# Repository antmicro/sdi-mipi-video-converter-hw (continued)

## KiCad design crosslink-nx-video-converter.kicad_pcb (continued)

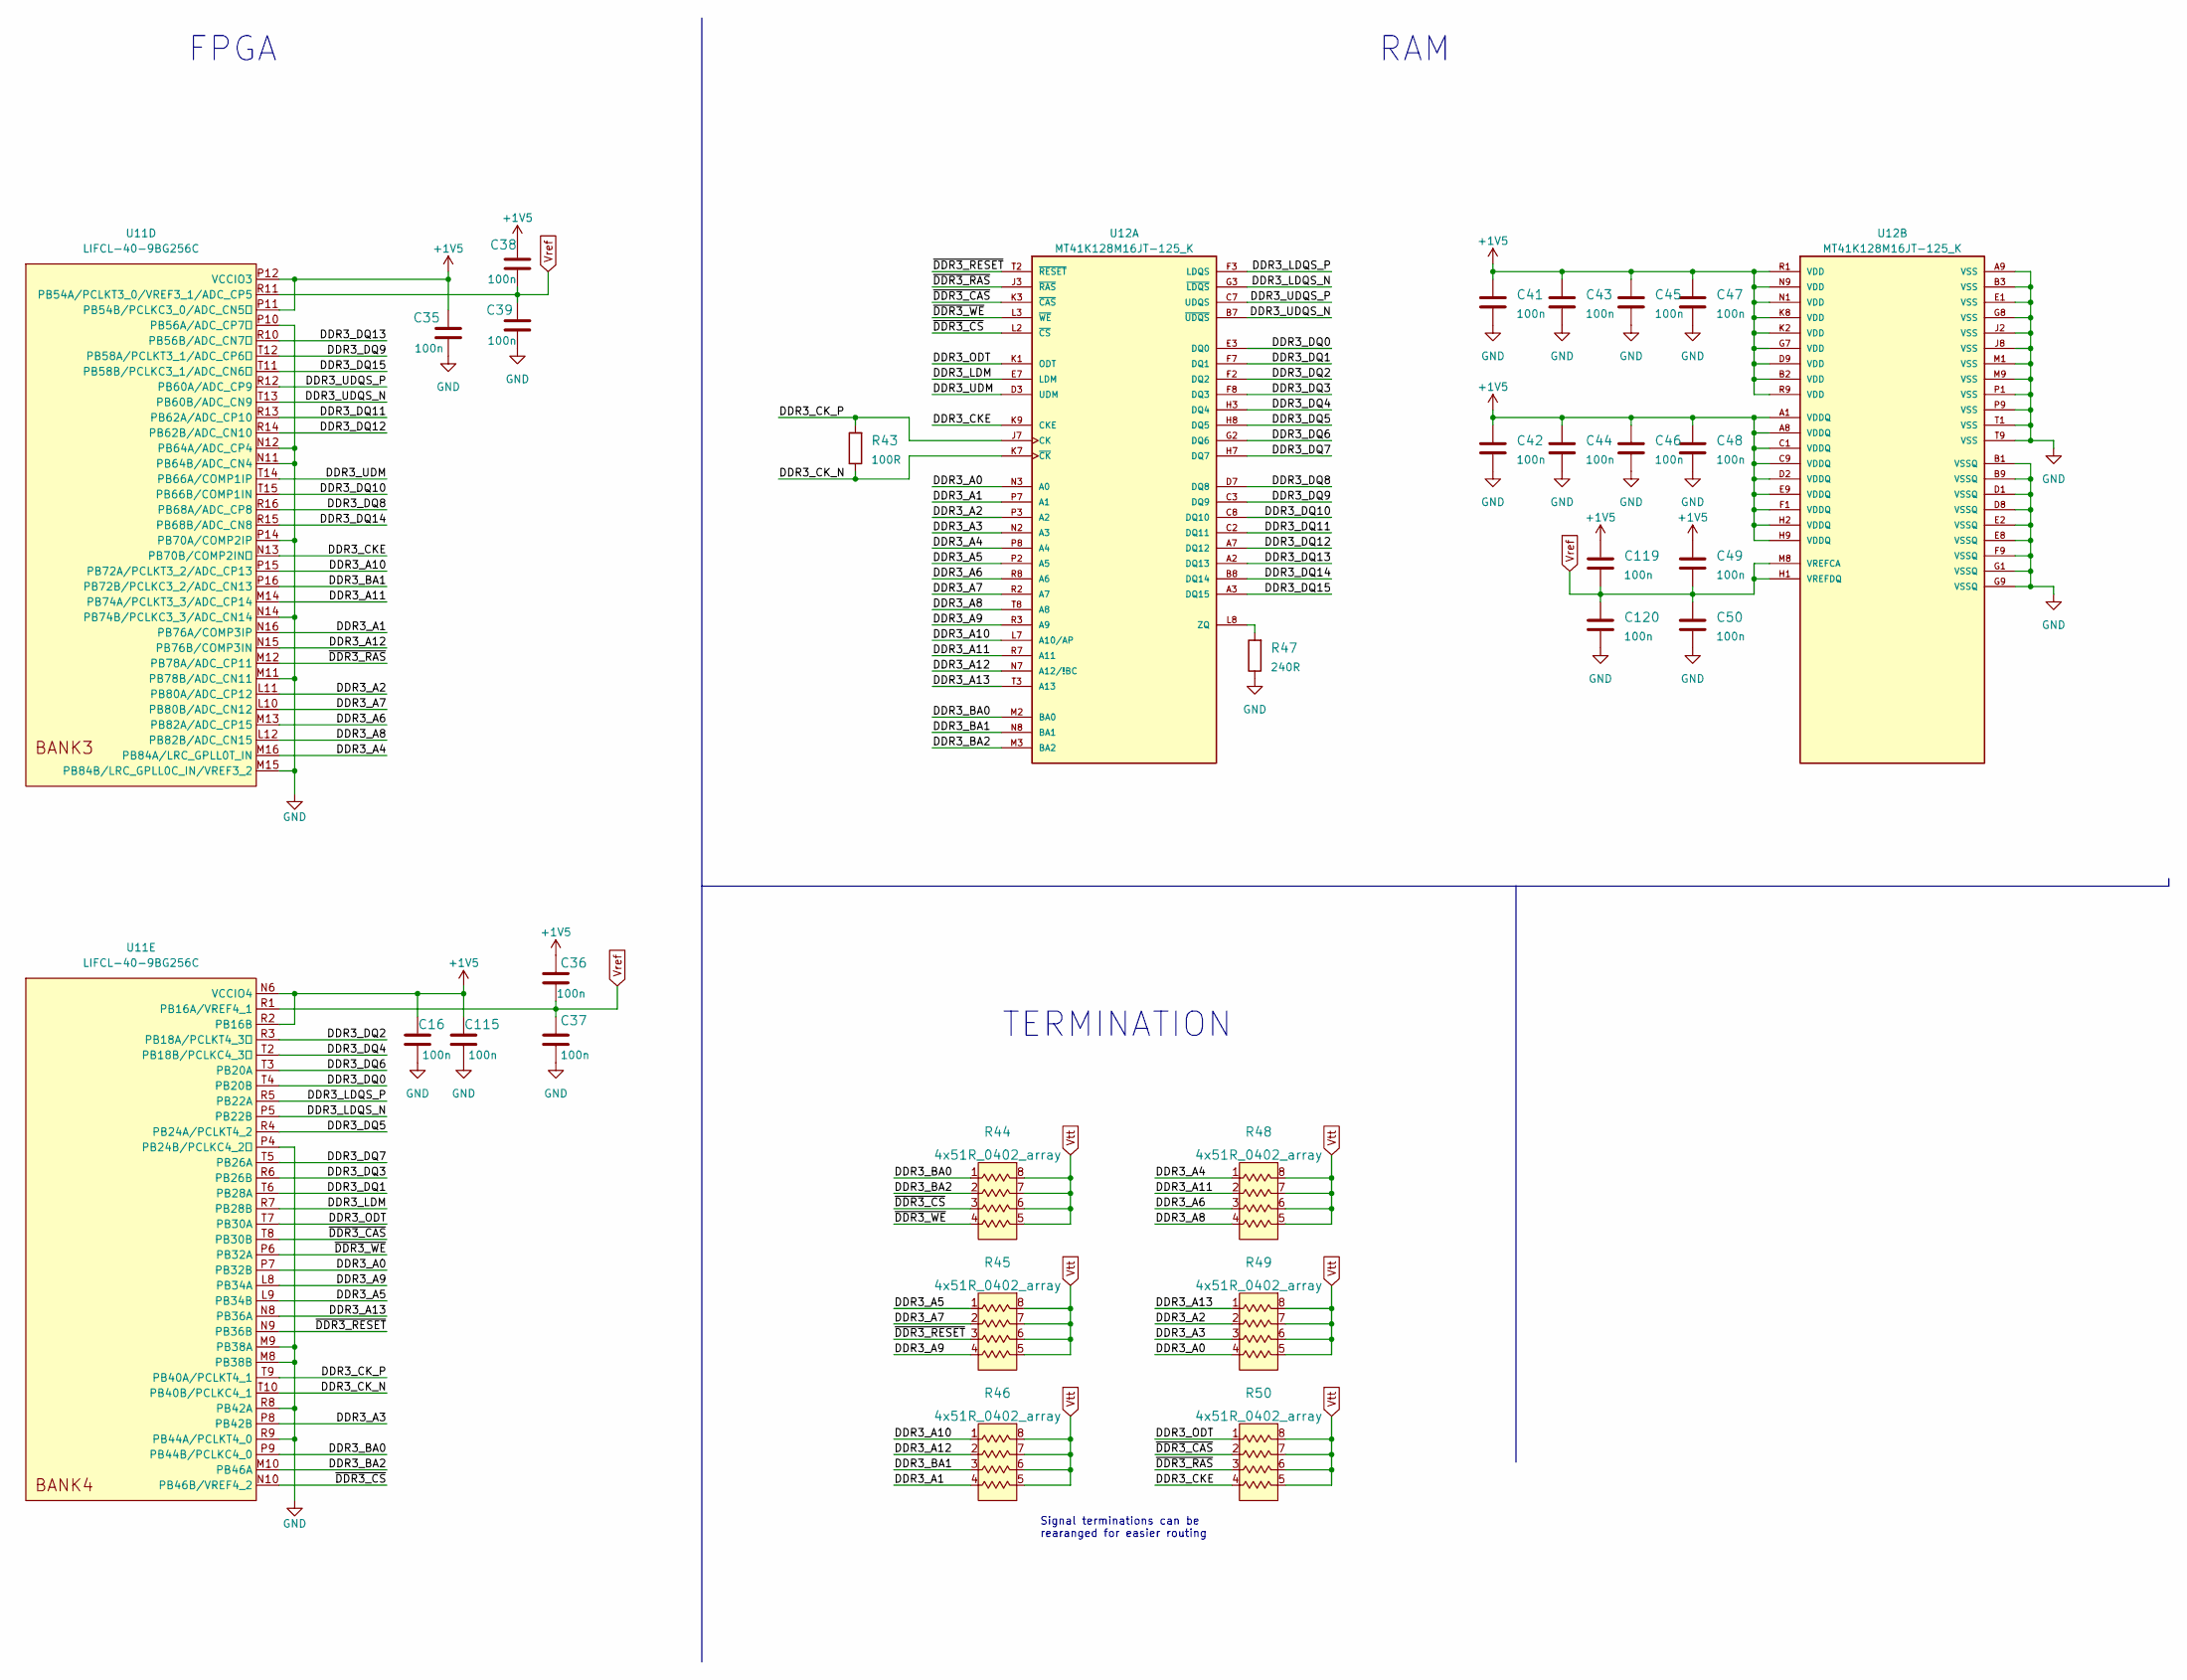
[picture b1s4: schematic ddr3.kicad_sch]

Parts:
C16, C35, C36, C37, C38, C39, C41, C42, C43, C44, C45, C46, C47, C48, C49, C50, C115, C119, C120: C_100n_0402; 0402-cap; MPN GRM155R61H104KE14D
R43: R_100R_0201; 0201-res; MPN CR0201AFW-1000GAS
R44, R45, R46, R48, R49, R50: 4x51R_0402_array; R_Array_4x0402; MPN EXB28V510JX
R47: R_240R_1%_0402; 0402-res; MPN RC0402FR-13240RL
U11: LIFCL-40-9BG256C; BGA-256_16x16_14.0x14.0mm; MPN LIFCL-40-9BG256C
U12: MT41K128M16JT-125_K; BGA80P96C6X16_800X1400X110; MPN MT41K128M16JT-125:K

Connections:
+1V5: C16.1, C35.1, C36.1, C38.1, C41.1, C42.1, C43.1, C44.1, C45.1, C46.1, C47.1, C48.1, C49.1, C115.1, C119.1, U11.N6 (VCCIO4), U11.P11 (PB54B/PCLKC3_0/ADC_CN5), U11.P12 (VCCIO3), U11.R2 (PB16B), U12.A1 (VDDQ), U12.A8 (VDDQ), U12.B2 (VDD), U12.C1 (VDDQ), U12.C9 (VDDQ), U12.D2 (VDDQ), U12.D9 (VDD), U12.E9 (VDDQ), U12.F1 (VDDQ), U12.G7 (VDD), U12.H2 (VDDQ), U12.H9 (VDDQ), U12.K2 (VDD), U12.K8 (VDD), U12.N1 (VDD), U12.N9 (VDD), U12.R1 (VDD), U12.R9 (VDD); also elsewhere on the board
/DDR3/DDR3_A0: R49.4, U11.P7 (PB32B), U12.N3 (A0)
/DDR3/DDR3_A1: R46.4, U11.N16 (PB76A/COMP3IP), U12.P7 (A1)
/DDR3/DDR3_A2: R49.2, U11.L11 (PB80A/ADC_CP12), U12.P3 (A2)
/DDR3/DDR3_A3: R49.3, U11.P8 (PB42B), U12.N2 (A3)
/DDR3/DDR3_A4: R48.1, U11.M16 (PB84A/LRC_GPLL0T_IN), U12.P8 (A4)
/DDR3/DDR3_A5: R45.1, U11.L9 (PB34B), U12.P2 (A5)
/DDR3/DDR3_A6: R48.3, U11.M13 (PB82A/ADC_CP15), U12.R8 (A6)
/DDR3/DDR3_A7: R45.2, U11.L10 (PB80B/ADC_CN12), U12.R2 (A7)
/DDR3/DDR3_A8: R48.4, U11.L12 (PB82B/ADC_CN15), U12.T8 (A8)
/DDR3/DDR3_A9: R45.4, U11.L8 (PB34A), U12.R3 (A9)
/DDR3/DDR3_A10: R46.1, U11.P15 (PB72A/PCLKT3_2/ADC_CP13), U12.L7 (A10/AP)
/DDR3/DDR3_A11: R48.2, U11.M14 (PB74A/PCLKT3_3/ADC_CP14), U12.R7 (A11)
/DDR3/DDR3_A12: R46.2, U11.N15 (PB76B/COMP3IN), U12.N7 (A12/!BC)
/DDR3/DDR3_A13: R49.1, U11.N8 (PB36A), U12.T3 (A13)
/DDR3/DDR3_BA0: R44.1, U11.P9 (PB44B/PCLKC4_0), U12.M2 (BA0)
/DDR3/DDR3_BA1: R46.3, U11.P16 (PB72B/PCLKC3_2/ADC_CN13), U12.N8 (BA1)
/DDR3/DDR3_BA2: R44.2, U11.M10 (PB46A), U12.M3 (BA2)
/DDR3/DDR3_CKE: R50.4, U11.N13 (PB70B/COMP2IN), U12.K9 (CKE)
/DDR3/DDR3_CK_N: R43.1, U11.T10 (PB40B/PCLKC4_1), U12.K7 (~CK)
/DDR3/DDR3_CK_P: R43.2, U11.T9 (PB40A/PCLKT4_1), U12.J7 (CK)
/DDR3/DDR3_DQ0: U11.T4 (PB20B), U12.E3 (DQ0)
/DDR3/DDR3_DQ1: U11.T6 (PB28A), U12.F7 (DQ1)
/DDR3/DDR3_DQ2: U11.R3 (PB18A/PCLKT4_3), U12.F2 (DQ2)
/DDR3/DDR3_DQ3: U11.R6 (PB26B), U12.F8 (DQ3)
/DDR3/DDR3_DQ4: U11.T2 (PB18B/PCLKC4_3), U12.H3 (DQ4)
/DDR3/DDR3_DQ5: U11.R4 (PB24A/PCLKT4_2), U12.H8 (DQ5)
/DDR3/DDR3_DQ6: U11.T3 (PB20A), U12.G2 (DQ6)
/DDR3/DDR3_DQ7: U11.T5 (PB26A), U12.H7 (DQ7)
/DDR3/DDR3_DQ8: U11.R16 (PB68A/ADC_CP8), U12.D7 (DQ8)
/DDR3/DDR3_DQ9: U11.T12 (PB58A/PCLKT3_1/ADC_CP6), U12.C3 (DQ9)
/DDR3/DDR3_DQ10: U11.T15 (PB66B/COMP1IN), U12.C8 (DQ10)
/DDR3/DDR3_DQ11: U11.R13 (PB62A/ADC_CP10), U12.C2 (DQ11)
/DDR3/DDR3_DQ12: U11.R14 (PB62B/ADC_CN10), U12.A7 (DQ12)
/DDR3/DDR3_DQ13: U11.R10 (PB56B/ADC_CN7), U12.A2 (DQ13)
/DDR3/DDR3_DQ14: U11.R15 (PB68B/ADC_CN8), U12.B8 (DQ14)
/DDR3/DDR3_DQ15: U11.T11 (PB58B/PCLKC3_1/ADC_CN6), U12.A3 (DQ15)
/DDR3/DDR3_LDM: U11.R7 (PB28B), U12.E7 (LDM)
/DDR3/DDR3_LDQS_N: U11.P5 (PB22B), U12.G3 (~LDQS)
/DDR3/DDR3_LDQS_P: U11.R5 (PB22A), U12.F3 (LDQS)
/DDR3/DDR3_ODT: R50.1, U11.T7 (PB30A), U12.K1 (ODT)
/DDR3/DDR3_UDM: U11.T14 (PB66A/COMP1IP), U12.D3 (UDM)
/DDR3/DDR3_UDQS_N: U11.T13 (PB60B/ADC_CN9), U12.B7 (~UDQS)
/DDR3/DDR3_UDQS_P: U11.R12 (PB60A/ADC_CP9), U12.C7 (UDQS)
/DDR3/~DDR3_CAS: R50.2, U11.T8 (PB30B), U12.K3 (~CAS)
/DDR3/~DDR3_CS: R44.3, U11.N10 (PB46B/VREF4_2), U12.L2 (~CS)
/DDR3/~DDR3_RAS: R50.3, U11.M12 (PB78A/ADC_CP11), U12.J3 (~RAS)
/DDR3/~DDR3_RESET: R45.3, U11.N9 (PB36B), U12.T2 (~RESET)
/DDR3/~DDR3_WE: R44.4, U11.P6 (PB32A), U12.L3 (~WE)
unnamed: R47.2, U12.L8 (ZQ)
Vref: C36.2, C37.1, C38.2, C39.1, C49.2, C50.1, C119.2, C120.1, U11.R1 (PB16A/VREF4_1), U11.R11 (PB54A/PCLKT3_0/VREF3_1/ADC_CP5), U12.H1 (VREFDQ), U12.M8 (VREFCA); also elsewhere on the board
Vtt: R44.5, R44.6, R44.7, R44.8, R45.5, R45.6, R45.7, R45.8, R46.5, R46.6, R46.7, R46.8, R48.5, R48.6, R48.7, R48.8, R49.5, R49.6, R49.7, R49.8, R50.5, R50.6, R50.7, R50.8; also elsewhere on the board

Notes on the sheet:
FPGA
TERMINATION
RAM
Signal terminations can be rearanged for easier routing

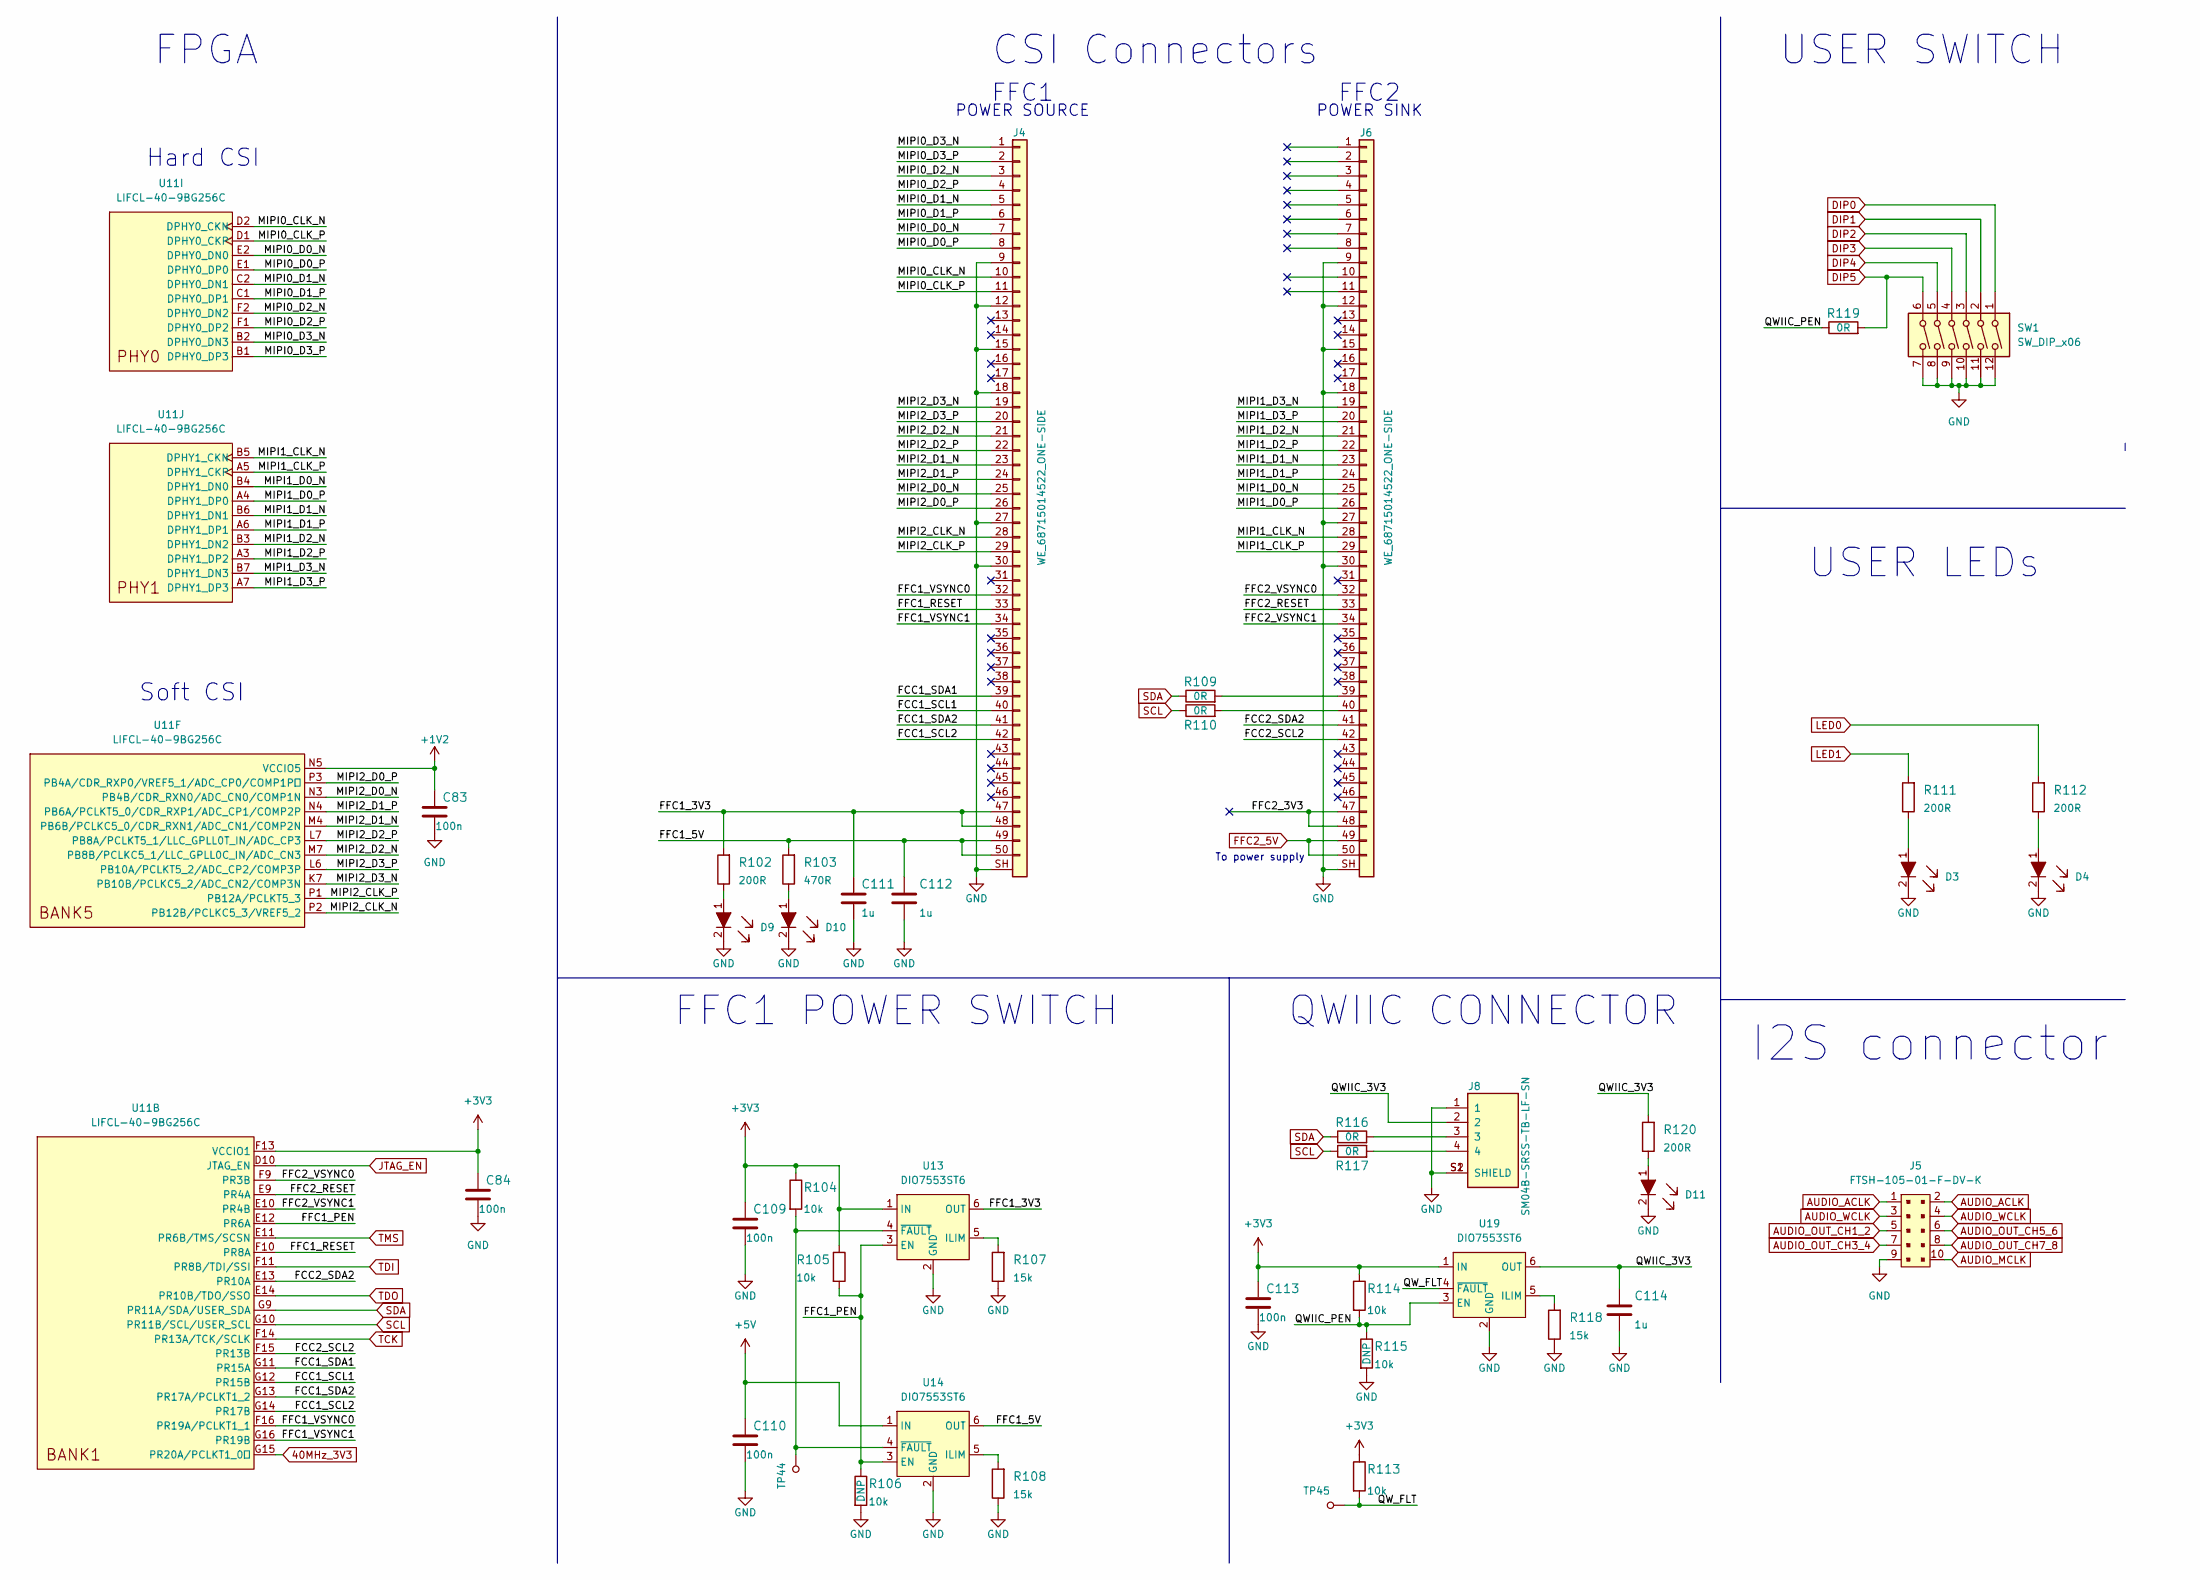
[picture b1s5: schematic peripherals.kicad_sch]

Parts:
C83, C84, C109, C110, C113: C_100n_0402; 0402-cap; MPN GRM155R61H104KE14D
C111, C112, C114: C_1u_0603; 0603-cap; MPN 0603YD105KAT2A
D3, D4, D9, D10, D11: LTST-C190GKT; LED_0603; MPN LTST-C190GKT
J4, J6: WE_68715014522_ONE-SIDE; MPN 68715014522
J5: FTSH-105-01-F-DV-K; PinHeader_2x5_P1.27_SMD; MPN FTSH-105-01-F-DV-K
J8: SM04B-SRSS-TB-LF-SN; MPN SM04B-SRSS-TB-LF-SN
R102, R111, R112, R120: R_200R_0603; 0603-res; MPN ERJ-UP3F2000V
R103: R_470R_0603; 0603-res; MPN CR0603-JW-471GLF
R104, R105, R106, R113, R114, R115: R_10k_0603; 0603-res; MPN CR0603-JW-103ELF
R107, R108, R118: R_15k_0603; 0603-res; MPN CR0603-FX-1502ELF
R109, R110, R116, R117, R119: R_0R_0603; 0603-res; MPN CR0603-J/-000ELF
SW1: SW_DIP_x06; SW_SPST_6_Slide_MCDHN-06F-T-V_P1.27mm; MPN MCDHN-06F-T-V
TP44, TP45: TP_SMD_0_75MM; Testpoint_smd_0_75mm
U11: LIFCL-40-9BG256C; BGA-256_16x16_14.0x14.0mm; MPN LIFCL-40-9BG256C
U13, U14, U19: DIO7553ST6; SOT23-6L; MPN DIO7553ST6

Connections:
40MHz_3V3: U11.G15 (PR20A/PCLKT1_0); also elsewhere on the board
+1V2: C83.1, U11.N5 (VCCIO5); also elsewhere on the board
+5V: C110.1, U14.1 (IN); also elsewhere on the board
/Peripherals/FCC1_SCL1: J4.40, U11.G12 (PR15B)
/Peripherals/FCC1_SCL2: J4.42, U11.G14 (PR17B)
/Peripherals/FCC1_SDA1: J4.39, U11.G11 (PR15A)
/Peripherals/FCC1_SDA2: J4.41, U11.G13 (PR17A/PCLKT1_2)
/Peripherals/FCC2_SCL2: J6.42, U11.F15 (PR13B)
/Peripherals/FCC2_SDA2: J6.41, U11.E13 (PR10A)
/Peripherals/FFC1_3V3: C111.1, J4.47, J4.48, R102.2, U13.6 (OUT)
/Peripherals/FFC1_5V: C112.1, J4.49, J4.50, R103.2, U14.6 (OUT)
/Peripherals/FFC1_PEN: R105.2, R106.1, U11.E12 (PR6A), U13.3 (EN), U14.3 (EN)
/Peripherals/FFC1_RESET: J4.33, U11.F10 (PR8A)
/Peripherals/FFC1_VSYNC0: J4.32, U11.F16 (PR19A/PCLKT1_1)
/Peripherals/FFC1_VSYNC1: J4.34, U11.G16 (PR19B)
/Peripherals/FFC2_3V3: J6.47, J6.48
/Peripherals/FFC2_RESET: J6.33, U11.E9 (PR4A)
/Peripherals/FFC2_VSYNC0: J6.32, U11.F9 (PR3B)
/Peripherals/FFC2_VSYNC1: J6.34, U11.E10 (PR4B)
/Peripherals/MIPI0_CLK_N: J4.10, U11.D2 (DPHY0_CKN)
/Peripherals/MIPI0_CLK_P: J4.11, U11.D1 (DPHY0_CKP)
/Peripherals/MIPI0_D0_N: J4.7, U11.E2 (DPHY0_DN0)
/Peripherals/MIPI0_D0_P: J4.8, U11.E1 (DPHY0_DP0)
/Peripherals/MIPI0_D1_N: J4.5, U11.C2 (DPHY0_DN1)
/Peripherals/MIPI0_D1_P: J4.6, U11.C1 (DPHY0_DP1)
/Peripherals/MIPI0_D2_N: J4.3, U11.F2 (DPHY0_DN2)
/Peripherals/MIPI0_D2_P: J4.4, U11.F1 (DPHY0_DP2)
/Peripherals/MIPI0_D3_N: J4.1, U11.B2 (DPHY0_DN3)
/Peripherals/MIPI0_D3_P: J4.2, U11.B1 (DPHY0_DP3)
/Peripherals/MIPI1_CLK_N: J6.28, U11.B5 (DPHY1_CKN)
/Peripherals/MIPI1_CLK_P: J6.29, U11.A5 (DPHY1_CKP)
/Peripherals/MIPI1_D0_N: J6.25, U11.B4 (DPHY1_DN0)
/Peripherals/MIPI1_D0_P: J6.26, U11.A4 (DPHY1_DP0)
/Peripherals/MIPI1_D1_N: J6.23, U11.B6 (DPHY1_DN1)
/Peripherals/MIPI1_D1_P: J6.24, U11.A6 (DPHY1_DP1)
/Peripherals/MIPI1_D2_N: J6.21, U11.B3 (DPHY1_DN2)
/Peripherals/MIPI1_D2_P: J6.22, U11.A3 (DPHY1_DP2)
/Peripherals/MIPI1_D3_N: J6.19, U11.B7 (DPHY1_DN3)
/Peripherals/MIPI1_D3_P: J6.20, U11.A7 (DPHY1_DP3)
/Peripherals/MIPI2_CLK_N: J4.28, U11.P2 (PB12B/PCLKC5_3/VREF5_2)
/Peripherals/MIPI2_CLK_P: J4.29, U11.P1 (PB12A/PCLKT5_3)
/Peripherals/MIPI2_D0_N: J4.25, U11.N3 (PB4B/CDR_RXN0/ADC_CN0/COMP1N)
/Peripherals/MIPI2_D0_P: J4.26, U11.P3 (PB4A/CDR_RXP0/VREF5_1/ADC_CP0/COMP1P)
/Peripherals/MIPI2_D1_N: J4.23, U11.M4 (PB6B/PCLKC5_0/CDR_RXN1/ADC_CN1/COMP2N)
/Peripherals/MIPI2_D1_P: J4.24, U11.N4 (PB6A/PCLKT5_0/CDR_RXP1/ADC_CP1/COMP2P)
/Peripherals/MIPI2_D2_N: J4.21, U11.M7 (PB8B/PCLKC5_1/LLC_GPLL0C_IN/ADC_CN3)
/Peripherals/MIPI2_D2_P: J4.22, U11.L7 (PB8A/PCLKT5_1/LLC_GPLL0T_IN/ADC_CP3)
/Peripherals/MIPI2_D3_N: J4.19, U11.K7 (PB10B/PCLKC5_2/ADC_CN2/COMP3N)
/Peripherals/MIPI2_D3_P: J4.20, U11.L6 (PB10A/PCLKT5_2/ADC_CP2/COMP3P)
/Peripherals/QWIIC_3V3: C114.1, J8.2, R120.2, U19.6 (OUT)
/Peripherals/QWIIC_PEN: R114.2, R115.1, R119.1, U19.3 (EN)
/Peripherals/QW_FLT: R113.2, TP45.1, U19.4 (~FAULT)
AUDIO_ACLK: J5.1, J5.2; also elsewhere on the board
AUDIO_MCLK: J5.10; also elsewhere on the board
AUDIO_OUT_CH1_2: J5.5; also elsewhere on the board
AUDIO_OUT_CH3_4: J5.7; also elsewhere on the board
AUDIO_OUT_CH5_6: J5.6; also elsewhere on the board
AUDIO_OUT_CH7_8: J5.8; also elsewhere on the board
AUDIO_WCLK: J5.3, J5.4; also elsewhere on the board
DIP0: SW1.1; also elsewhere on the board
DIP1: SW1.2; also elsewhere on the board
DIP2: SW1.3; also elsewhere on the board
DIP3: SW1.4; also elsewhere on the board
DIP4: SW1.5; also elsewhere on the board
DIP5: R119.2, SW1.6; also elsewhere on the board
FFC2_5V: J6.49, J6.50; also elsewhere on the board
JTAG_EN: U11.D10 (JTAG_EN); also elsewhere on the board
LED0: R112.2; also elsewhere on the board
LED1: R111.2; also elsewhere on the board
unnamed: D3.1, R111.1
unnamed: D4.1, R112.1
unnamed: D9.1, R102.1
unnamed: D10.1, R103.1
unnamed: D11.1, R120.1
unnamed: J6.39, R109.2
unnamed: J6.40, R110.2
unnamed: J8.3, R116.2
unnamed: J8.4, R117.2
unnamed: R104.2, TP44.1, U13.4 (~FAULT), U14.4 (~FAULT)
unnamed: R107.2, U13.5 (ILIM)
unnamed: R108.2, U14.5 (ILIM)
unnamed: R118.2, U19.5 (ILIM)
SCL: R110.1, R117.1, U11.G10 (PR11B/SCL/USER_SCL); also elsewhere on the board
SDA: R109.1, R116.1, U11.G9 (PR11A/SDA/USER_SDA); also elsewhere on the board
TCK: U11.F14 (PR13A/TCK/SCLK); also elsewhere on the board
TDI: U11.F11 (PR8B/TDI/SSI); also elsewhere on the board
TDO: U11.E14 (PR10B/TDO/SSO); also elsewhere on the board
TMS: U11.E11 (PR6B/TMS/SCSN); also elsewhere on the board

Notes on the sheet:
Soft CSI
FFC1 POWER SWITCH
POWER SOURCE
QWIIC CONNECTOR
FPGA
FFC1
USER LEDs
CSI Connectors
I2S connector
USER SWITCH
FFC2
Hard CSI
To power supply
POWER SINK

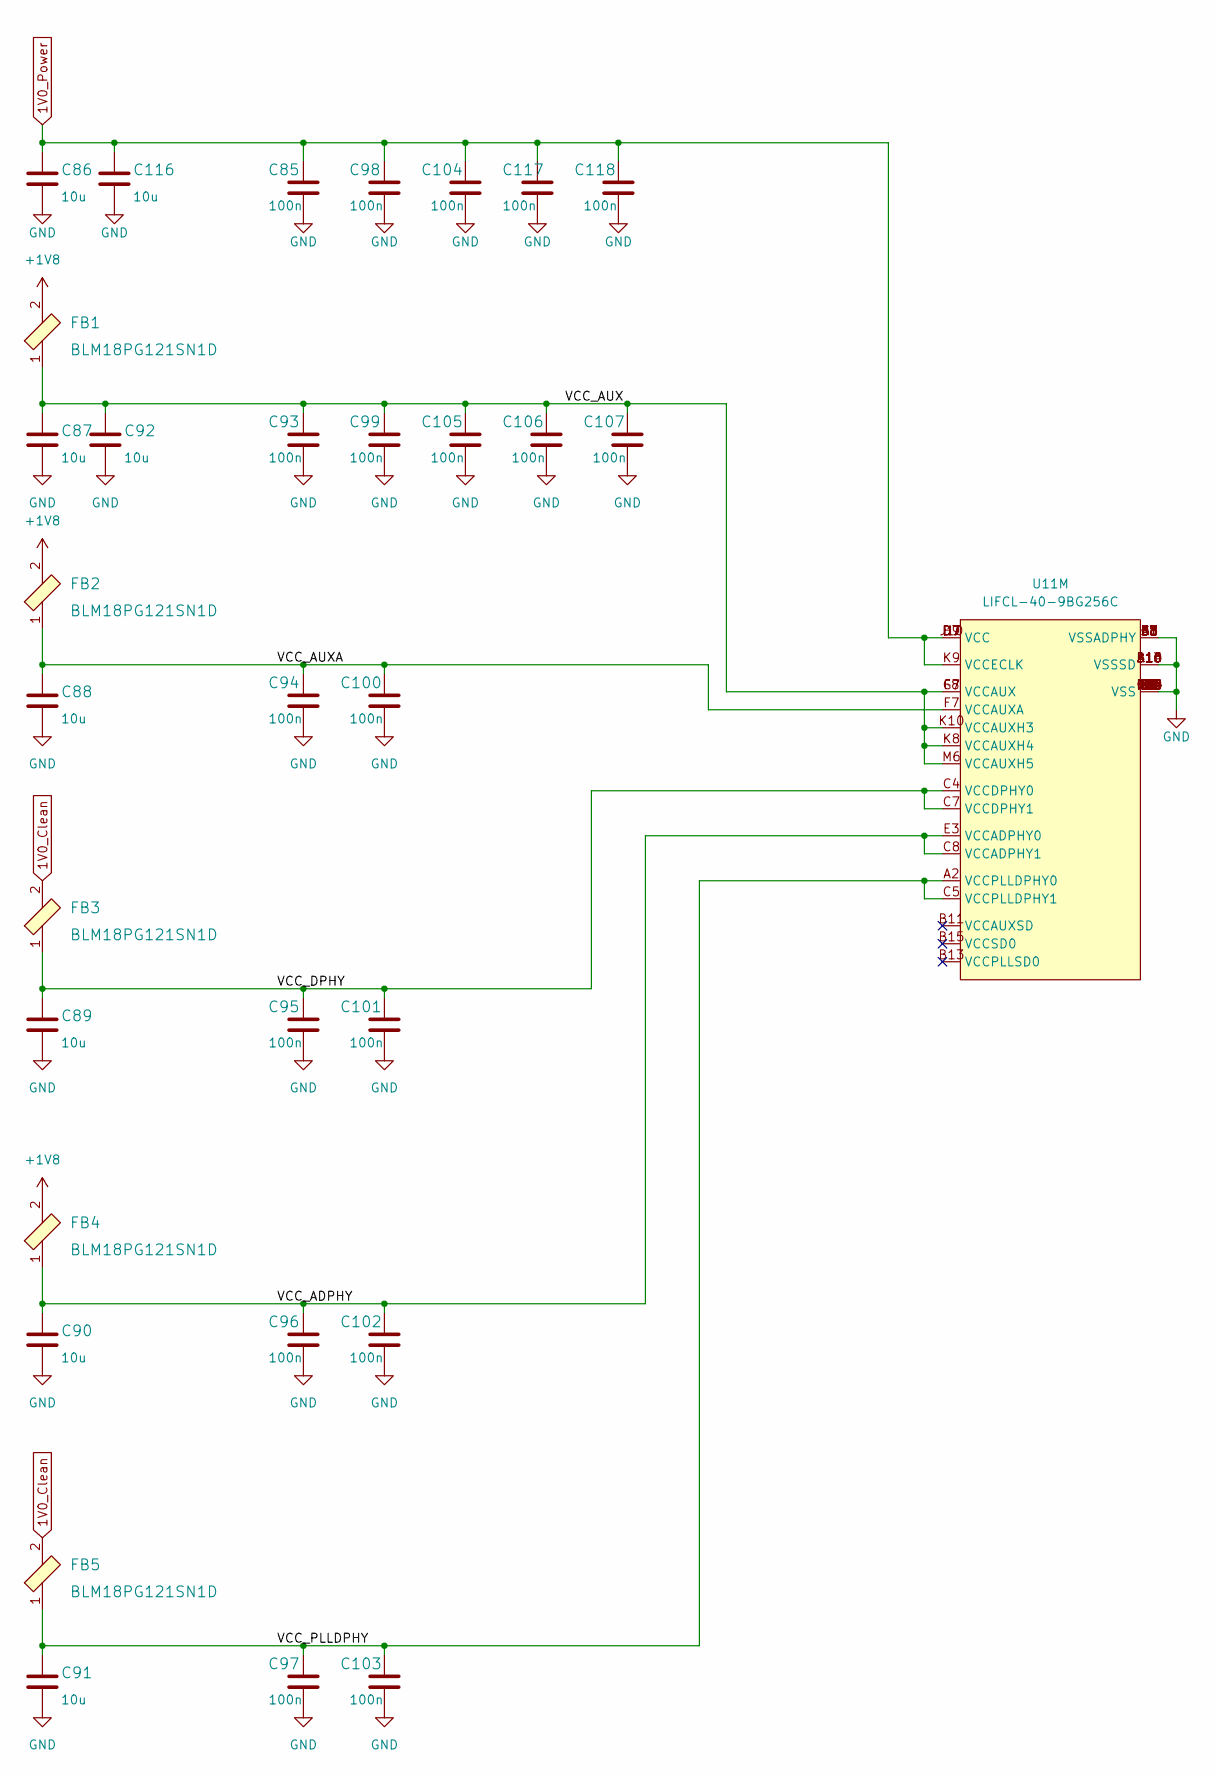
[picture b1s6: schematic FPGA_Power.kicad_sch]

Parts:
C85, C93, C94, C95, C96, C97, C98, C99, C100, C101, C102, C103, C104, C105, C106, C107, C117, C118: C_100n_0402; 0402-cap; MPN GRM155R61H104KE14D
C86, C87, C88, C89, C90, C91, C92, C116: C_10u_0603; 0603-cap; MPN GRM188R61A106KE69D
FB1, FB2, FB3, FB4, FB5: BLM18PG121SN1D; 0603-res; MPN BLM18PG121SN1D
U11: LIFCL-40-9BG256C; BGA-256_16x16_14.0x14.0mm; MPN LIFCL-40-9BG256C

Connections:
/FPGA Power/VCC_ADPHY: C90.1, C96.1, C102.1, FB4.1, U11.C8 (VCCADPHY1), U11.E3 (VCCADPHY0)
/FPGA Power/VCC_AUX: C87.1, C92.1, C93.1, C99.1, C105.1, C106.1, C107.1, FB1.1, U11.F8 (VCCAUX), U11.G7 (VCCAUX), U11.K8 (VCCAUXH4), U11.K10 (VCCAUXH3), U11.M6 (VCCAUXH5)
/FPGA Power/VCC_AUXA: C88.1, C94.1, C100.1, FB2.1, U11.F7 (VCCAUXA)
/FPGA Power/VCC_DPHY: C89.1, C95.1, C101.1, FB3.1, U11.C4 (VCCDPHY0), U11.C7 (VCCDPHY1)
/FPGA Power/VCC_PLLDPHY: C91.1, C97.1, C103.1, FB5.1, U11.A2 (VCCPLLDPHY0), U11.C5 (VCCPLLDPHY1)

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
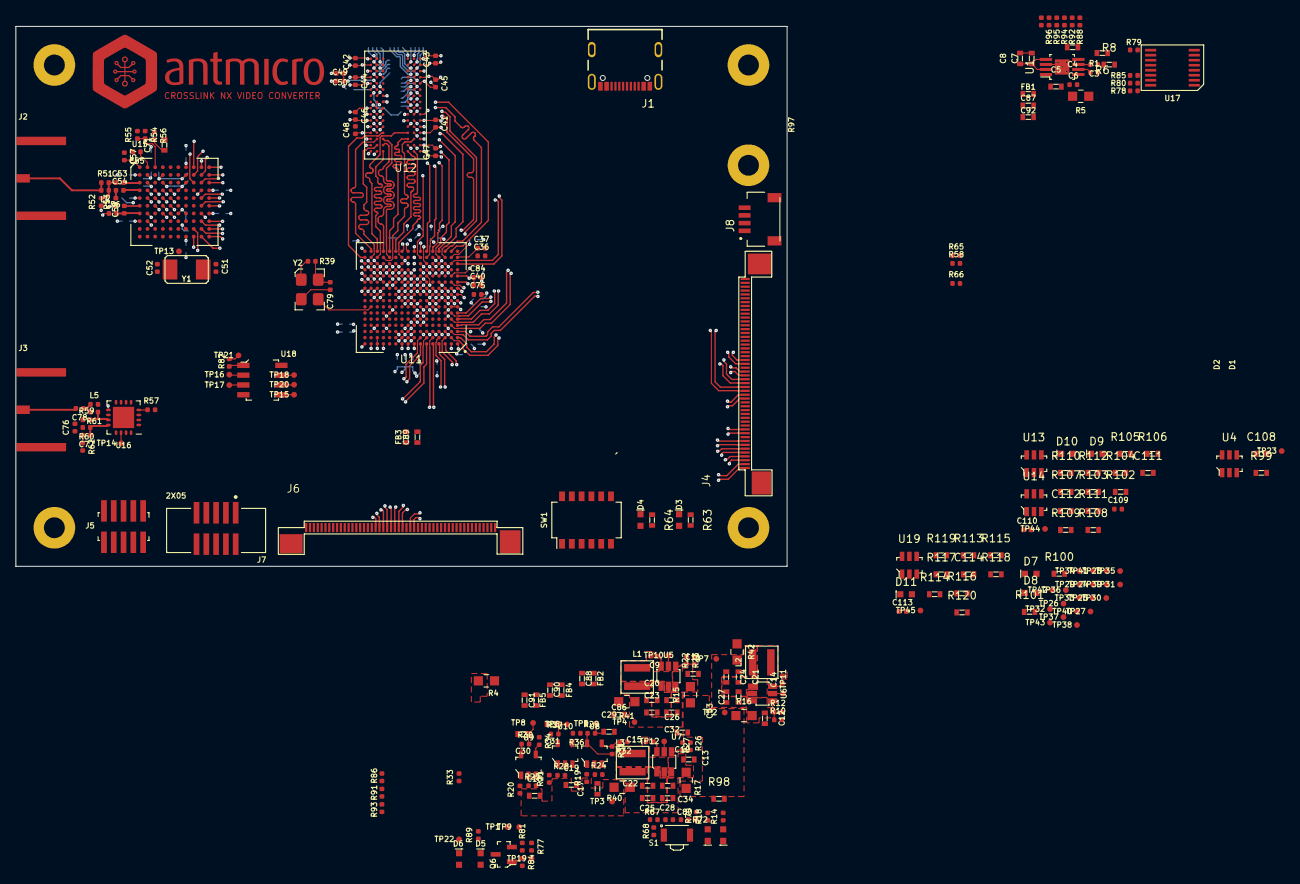
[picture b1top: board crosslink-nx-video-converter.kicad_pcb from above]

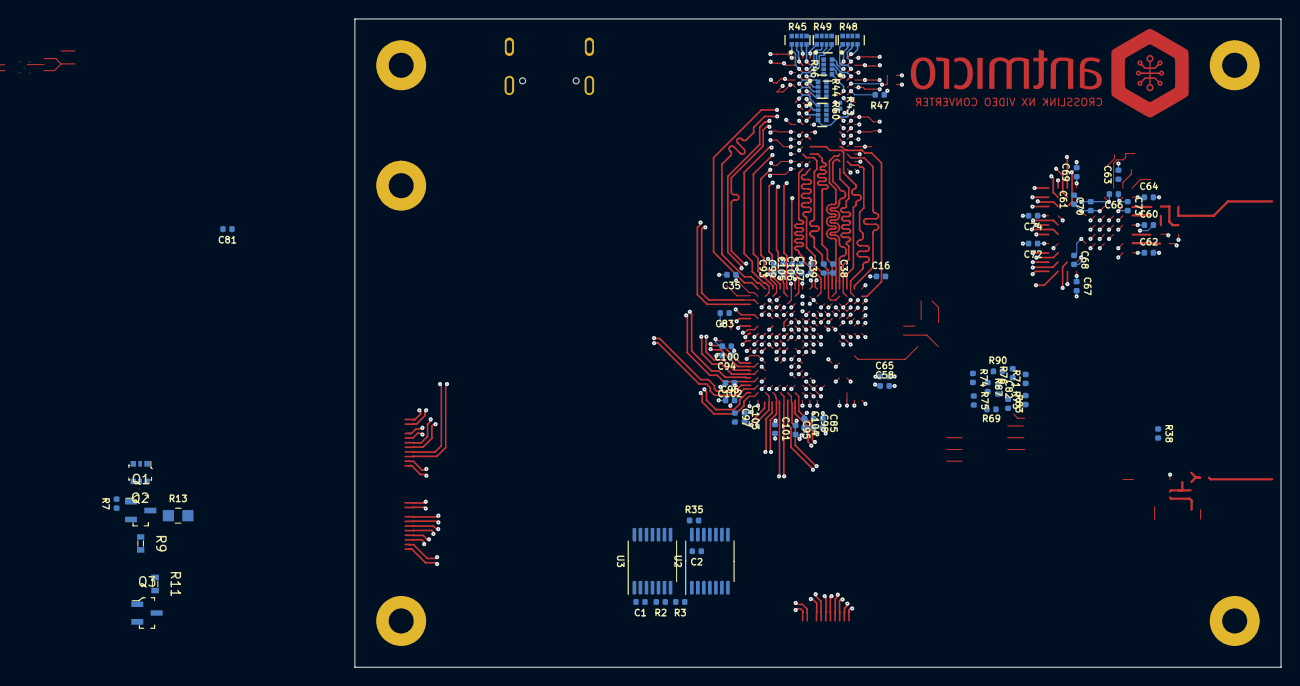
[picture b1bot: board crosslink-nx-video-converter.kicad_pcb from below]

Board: 8 copper layers, 100.0 x 70.0 mm, 335 parts (70 on the bottom side), 302 nets.

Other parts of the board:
R73, R74: R_0R_0402; 0402-res

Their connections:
/FPGA/SPI_DQ2: R73.1; also elsewhere on the board
/FPGA/SPI_DQ3: R74.2; also elsewhere on the board

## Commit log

2022-07-06 Added 3.3V and 1V0_Power SMPSs
2022-07-06 Created hierarchy
2022-07-06 Redesigned 3.3V supply taking into the consideration reduced power requirements
2022-07-07 Added DRAM SMPS
2022-07-07 Added LDOs
2022-11-25 Completed schematic of MT41K128M16JT memory module
2022-11-25 Fixed differential pair names
2022-11-25 Added DDR3 Vtt and Vref regulator
2022-11-25 Recalculated PSU SMPSs ratings
2022-11-25 Fixed VREF connection
2022-11-25 Made a connection between DDR3 and fpga on the schematic
2022-11-25 Connected FPGA to power supply and added power filtering
2022-11-25 Connected soft MIPI CSI to FPGA
2022-11-25 Fixed net labels
2022-11-25 Connected Semtech to the power supply, cable driver and the FPGA
2022-11-25 Made PCB mockup
2022-11-25 Added power testpoints
2022-11-25 Added indicator LEDs and user switch
2022-11-25 Added visualization config
2022-11-25 Added optional oscillator
2022-11-25 Replaced RPi camera connector with 50pin one, modified PSU with ability of being supplied via FFC
2022-11-25 Added FPGA configuration circuitry
2022-11-25 Added input and output termination
2022-11-25 Small I2C connection fix
2022-11-25 Connected EN pins on PSU schematic
2022-11-25 Small fix to power switch circuitry
2022-11-25 Removed components outside PCB
2022-11-25 Added loclib
2022-11-25 Updated 3D vis config
2022-11-25 Divided FPGA into multiple blocks
2022-11-25 Modified power indicator and connected unused pins
2022-11-25 Added updated block diagram
2022-11-25 Switched voltages to support DDR3 and RPC memories
2022-11-25 Preliminary FPGA fanout
2022-11-25 Assigned net classes
2022-11-25 More fanout
2022-11-25 Placed components
2022-11-25 Finished component placement
2022-11-25 Updated block diagrams
2022-11-25 Loclib
2022-11-25 Changed PCB size
2022-11-25 Added QWIIC connector
2022-11-25 Routed DDR3 C&A
2022-11-25 Small fixes to high speed signals
2022-11-25 Changed DC jack to USB-C, added power switch for FFC1, fixed MP20073
2022-11-25 Routed SDI data interface
2022-11-25 Routed hard CSI
2022-11-25 Length matched most high speed interfaces
2022-11-25 Rerouted some DDR3 signals
2022-11-25 Added testpoints and LEDs for SDI circuitry
2022-11-25 Fixed SDI top impedance
2022-11-25 Added In.1 gnd plane
2022-11-25 Power plane layout
2022-11-25 Routed rest of low speed signals
2022-11-25 Improved DC-DC cooling
2022-11-25 Completed the layout of the PSU
2022-11-25 Routed Semtec status and control signals
2022-11-25 Added more gnd vias
2022-11-25 Added connector silkscreen description
2022-11-25 Added revision number and name date to PCB
2022-11-25 Fix FPGA power supply
2022-11-25 Power planes initial layout
2022-11-25 Fixed CSI, SDI data and DDR length matching
2022-11-25 Small clearence fix
2022-11-25 Routed low speed FFC signals, routed JTAG
2022-11-25 Fixed few DRC issues, replaced one power trace with zone
2022-11-25 Fixed via size, changed connector placement
2022-11-25 Routed flash memory
2022-11-25 Routed I2S
2022-11-25 Fixed component silkscreen
2022-11-25 Fixed to CSI layout and DDR impedance
2022-11-25 Started power supply layoyt
2022-11-25 Placed decoupling capacitors
2022-11-25 Fixed all DRC errors
2022-11-25 Fixed impedance issues
2022-11-25 Added gpio connector
2022-11-25 Small layout fixes
2022-11-25 DRC fixes
2022-11-25 Added FT230XQ-R for USB connectivity
2022-11-25 Added revision and title to the schematic sheets
2022-11-25 Added 0R to low speed FFC signals, moved few testpoints
2022-11-25 Added pdf schematic
2022-11-25 Created loclib
2022-11-25 Added DRC rules and fixed track width/gap width/length matching issues
2022-11-25 Added optional header connector for GPIO
2022-11-25 Removed unnecessary files
2022-11-25 Added USB power cap, fixed USB routing, moved gpio header connector back
2022-11-25 Added PCB revision string
2022-11-25 Changed BNC connector 3d model
2022-11-25 Updated libs to include new 3d models
2022-11-25 Updated PCB naming
2022-11-25 Created README
2022-11-25 README: fix naming
2022-11-25 Review README
2022-11-25 Update tracks bent by vias - after EC validation
2022-11-30 Update PCB routing
    - apply new DRC
    - add FPGA package delay to the high speed traces tunning
    - improve GND and power planes
2022-12-12 Update project naming convention
2022-12-12 Ignore backups
2022-12-12 Bump to 1.1.0, update naming
2022-12-12 Update U11/LIFCL-40-9BG256C footprint property
2022-12-12 Resize image
2022-12-12 README: add MPNs for crucial components
2022-12-12 Add 3DVis
2022-12-12 Add logotypes to schematics
2022-12-12 Update 3DVis
2022-12-12 Add PDF schematic
2022-12-20 Update naming convention
2022-12-20 README: update 3D Vis
2022-12-20 Rescale image
2022-12-22 README: Add photo
2023-01-03 Fixed mirrored vtt regulator component
2023-01-30 Added mux on SPI
2023-01-30 Added SPI mux to layout
2023-01-30 Revision bumped to 1.1.2
2023-03-08 Add diagram
2023-10-12 Apply component standarization
2023-10-12 Bump revision to 1.1.4
2023-10-12 Resolve ERC
2023-10-12 Cleanup silks overlapping other graphical items
2023-10-12 Update TMUX1574RSVR footprint
2023-10-12 [#48149] Change LIFCL footprint for footprint with markings
2023-10-12 [#48149] Update GS297 and LIFCL symbols, update local lib
2023-10-12 README: bump copyright date, add badge
2023-10-12 Cleanup
2023-10-12 Update SCH and PCB revision date
2023-10-13 Add OHP assets, update PDF schematic
2023-11-10 Add stackup
2024-02-23 [#55653] Convert to KiCad7
2024-02-23 [#55653] Update SM04B-SRSS-TB(LF)(SN)
2024-02-23 [#55653] Update SM06B-GHS-TB(LF)(SN)
2024-02-23 [#55653] Update TSM-106-01-T-SH
2024-02-23 [#55653] Update MT41K128M16JT-125:K
2024-02-23 [#55653] Update FT230X_QFN
2024-02-23 [#55653] Update TMUX1574RSVR
2024-02-23 [#55653] Update Conn_JST_GH_1x6_SM06B-SRSS-TB-LF-SN
2024-02-23 [#55653] Loclib
2024-02-23 [#55653] Fix LIFCL-40
2024-02-23 [#55653] Add OHP assets
2024-02-26 [#55653] Fix manufacturer of LIFCL-40
2024-02-26 [#55653] Update data.json
2024-04-02 Fix symbols/footprint coordinates
2025-01-15 [#71605] Update assets
2025-10-30 [#82595] Project refresh 81589
2025-11-03 Correct components
